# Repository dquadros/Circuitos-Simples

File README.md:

# Circuitos-Simples
Circuitos simples para montagem em oficinas

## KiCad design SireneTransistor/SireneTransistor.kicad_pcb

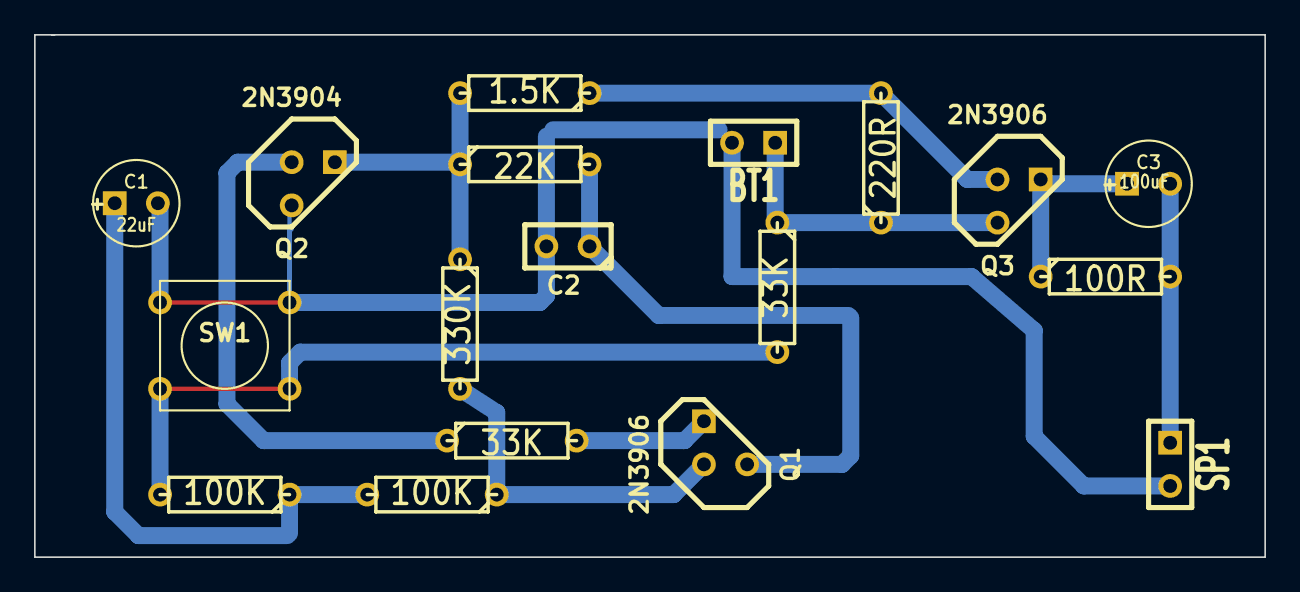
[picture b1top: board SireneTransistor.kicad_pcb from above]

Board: 2 copper layers, 72.4 x 30.7 mm, 18 parts (0 on the bottom side), 12 nets.

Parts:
BT1: 9V; SIL-2
C1: 22uF; C1V5
C2: 0,1uF; C1
C3: 100uF; C1V5
Q1, Q3: 2N3906; TO92-123
Q2: 2N3904; TO92-123
R1, R6: 33K; R3
R2, R3: 100K; R3
R4: 330K; R3
R5: 22K; R3
R7: 1.5K; R3
R8: 220R; R3
R9: 100R; R3
SP1: SPEAKER; SIL-2
SW1: SW_PUSH_SMALL

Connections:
unnamed: C2.1, Q1.1, R5.2
unnamed: Q2.3, R4.1, R5.1, R7.2
unnamed: Q3.2, R7.1, R8.2
unnamed: C3.1, Q3.3, R9.1
unnamed: C3.2, R9.2, SP1.1
unnamed: BT1.1, Q3.1, R1.1, R8.1
unnamed: Q2.2, R6.1
unnamed: Q1.3, R6.2
unnamed: Q1.2, R3.1, R4.2
unnamed: C1.1, R2.1, R3.2
unnamed: BT1.2, C1.2, C2.2, Q2.1, SP1.2, SW1.1
unnamed: R1.2, R2.2, SW1.2

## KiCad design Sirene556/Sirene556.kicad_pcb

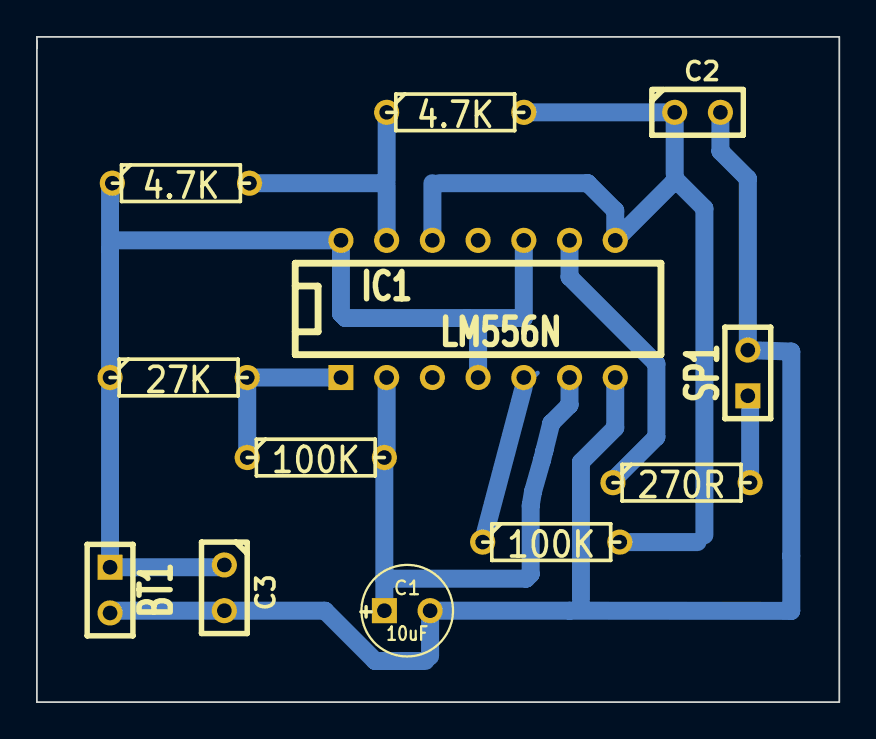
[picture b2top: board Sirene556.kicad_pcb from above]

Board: 2 copper layers, 44.6 x 37.0 mm, 12 parts (0 on the bottom side), 9 nets.

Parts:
BT1: BATTERY; SIL-2
C1: 10uF; C1V5
C2, C3: 0.1uF; C1
IC1: LM556N; DIP-14__300
R1: 27K; R3
R2, R3: 100K; R3
R4, R5: 4.7K; R3
R6: 270R; R3
SP1: SPEAKER; SIL-2

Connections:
unnamed: C1.1, IC1.2, IC1.6, R2.2
unnamed: C2.1, IC1.8, IC1.12, R3.2, R5.2
unnamed: IC1.5, R3.1
unnamed: IC1.1, R1.2, R2.1
unnamed: R6.2, SP1.1
unnamed: IC1.13, R4.2, R5.1
unnamed: IC1.9, R6.1
unnamed: BT1.1, C3.1, IC1.4, IC1.10, IC1.14, R1.1, R4.1
unnamed: BT1.2, C1.2, C2.2, C3.2, IC1.7, SP1.2

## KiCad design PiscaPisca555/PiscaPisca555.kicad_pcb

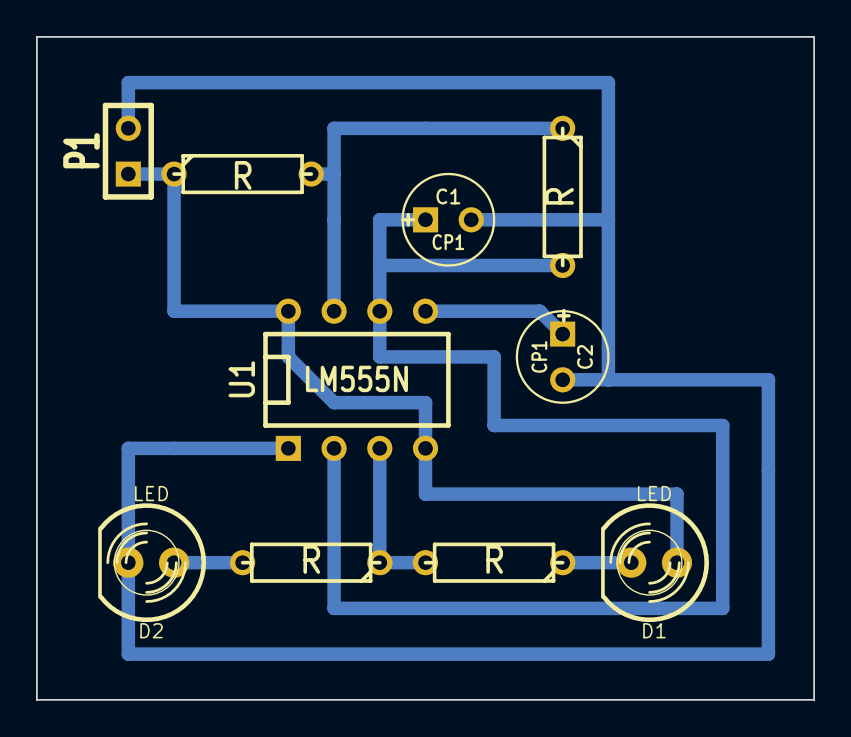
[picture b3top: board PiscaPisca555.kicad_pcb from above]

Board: 2 copper layers, 43.2 x 36.8 mm, 10 parts (0 on the bottom side), 8 nets.

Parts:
C1, C2: CP1; C1V5
D1, D2: LED; LED-5MM
P1: CONN_2; SIL-2
R1, R2, R3, R4: R; R3
U1: LM555N; DIP-8__300

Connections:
+9V: D1.1, P1.1, R1.1, U1.4, U1.8
GND: C1.2, C2.2, D2.2, P1.2, U1.1
unnamed: C1.1, R2.2, U1.2, U1.6
unnamed: R1.2, R2.1, U1.7
unnamed: C2.1, U1.5
unnamed: D1.2, R3.1
unnamed: D2.1, R4.2
unnamed: R3.2, R4.1, U1.3

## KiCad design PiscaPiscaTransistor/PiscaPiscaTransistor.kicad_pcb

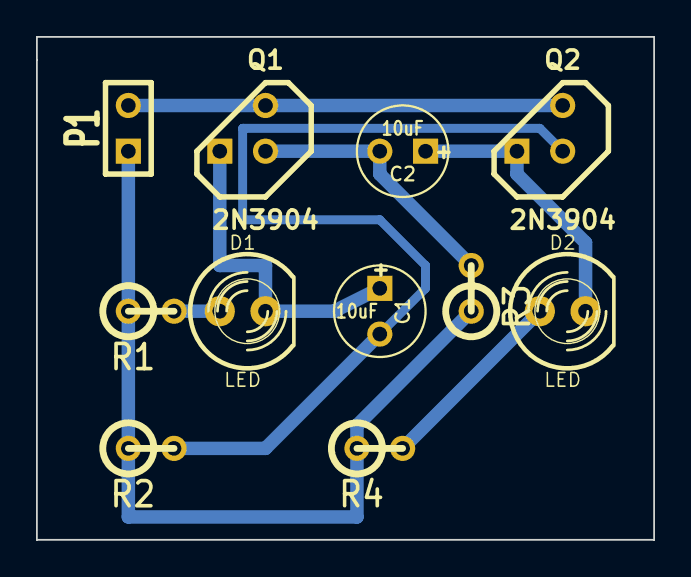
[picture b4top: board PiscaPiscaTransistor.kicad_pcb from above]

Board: 2 copper layers, 34.3 x 27.9 mm, 11 parts (0 on the bottom side), 8 nets.

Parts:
C1, C2: 10uF; C1V5
D1, D2: LED; LED-5MM
P1: CONN_2; SIL-2
Q1, Q2: 2N3904; TO92-123
R1, R4: 560; R1
R2, R3: 39K; R1

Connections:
+BATT: P1.1, R1.1, R2.1, R3.1, R4.1
GND: P1.2, Q1.1, Q2.1
unnamed: D1.1, R1.2
unnamed: C2.1, D2.2, Q2.3
unnamed: C2.2, Q1.2, R3.2
unnamed: C1.2, Q2.2, R2.2
unnamed: C1.1, D1.2, Q1.3
unnamed: D2.1, R4.2

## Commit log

2015-01-27 Versao inicial do Pisca Pisca com Transistor.
2015-01-30 Versao inicial
2015-02-19 Incluida Sirene 556
2015-02-20 Versao inicial Sirene Transistor
2015-02-20 Acerto da espessura das trilhas
